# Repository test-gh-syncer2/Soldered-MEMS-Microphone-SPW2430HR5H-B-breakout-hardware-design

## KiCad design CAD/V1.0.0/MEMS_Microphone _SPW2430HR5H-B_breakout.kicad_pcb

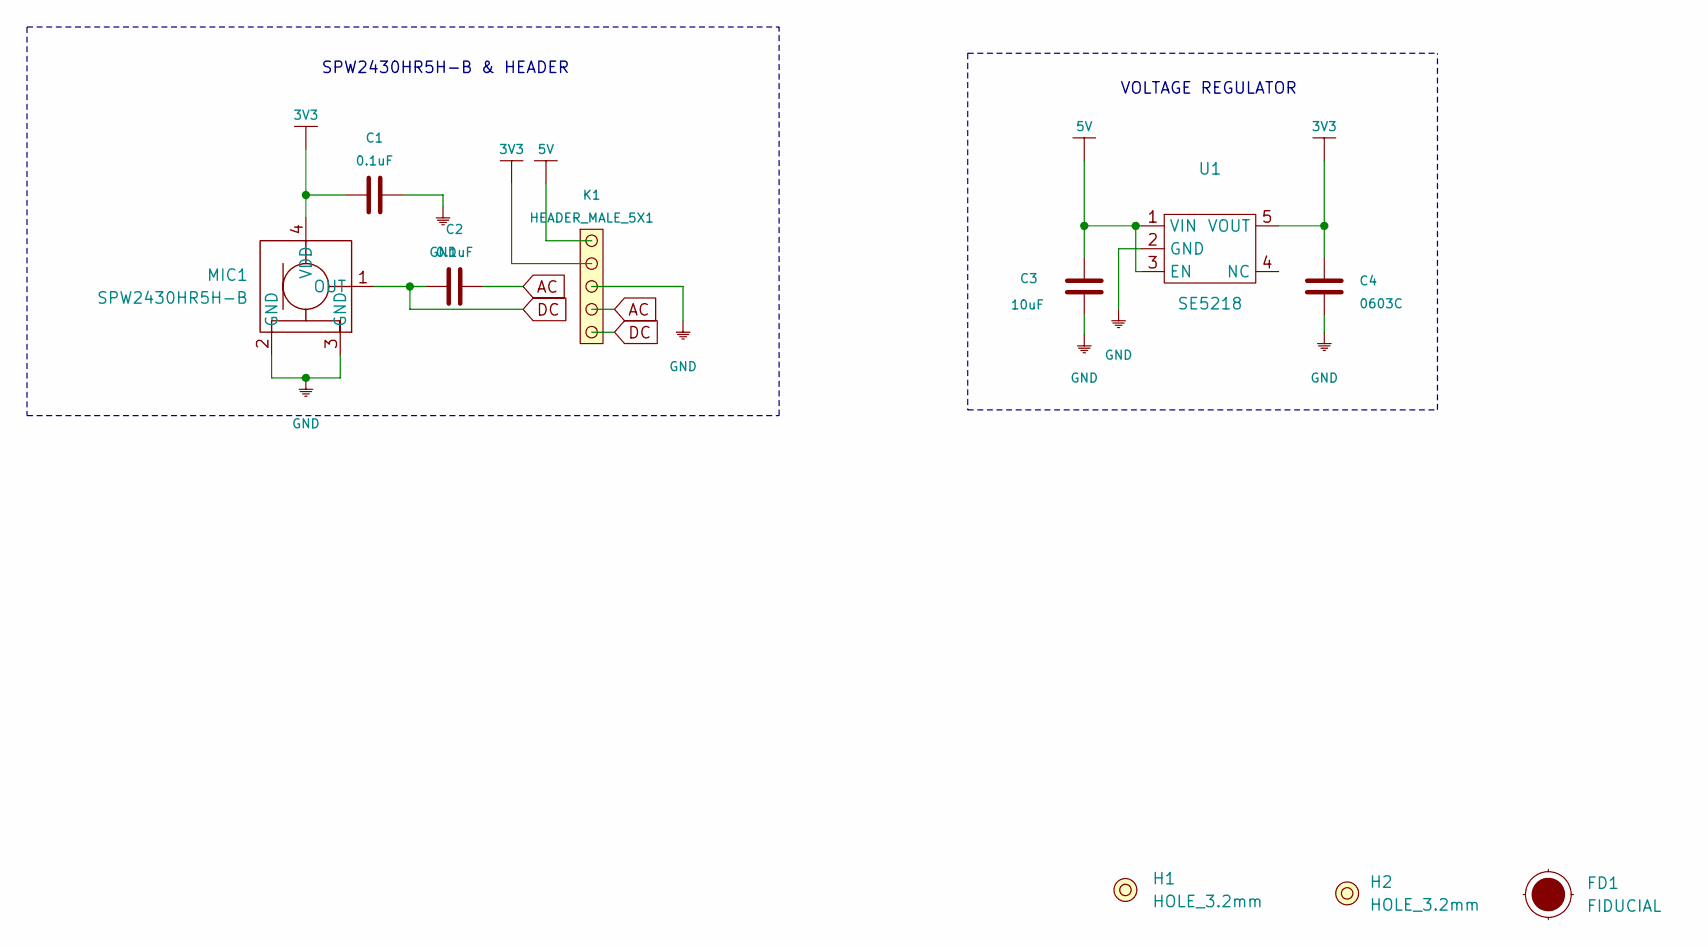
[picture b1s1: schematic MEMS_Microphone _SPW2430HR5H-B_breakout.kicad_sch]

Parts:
C1, C2: 0.1uF; 0603C
C3: 10uF; 0603C
C4: 0603C
FD1: FIDUCIAL; FIDUCIAL_23
H1, H2: HOLE_3.2mm
K1: HEADER_MALE_5X1
MIC1: SPW2430HR5H-B
U1: SE5218; SOT-23-5

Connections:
3V3: C1.1, C4.2, K1.4, MIC1.4 (VDD), U1.5 (VOUT)
5V: C3.2, K1.5, U1.1 (VIN), U1.3 (EN)
AC: C2.2, K1.2
DC: C2.1, K1.1, MIC1.1 (OUT)
GND: C1.2, C3.1, C4.1, K1.3, MIC1.2 (GND), MIC1.3 (GND), U1.2 (GND)

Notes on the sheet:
SPW2430HR5H-B & HEADER
VOLTAGE REGULATOR

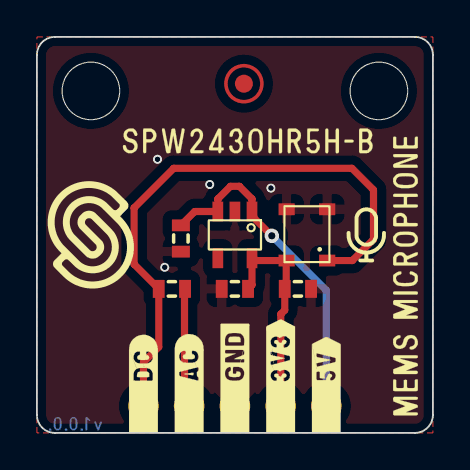
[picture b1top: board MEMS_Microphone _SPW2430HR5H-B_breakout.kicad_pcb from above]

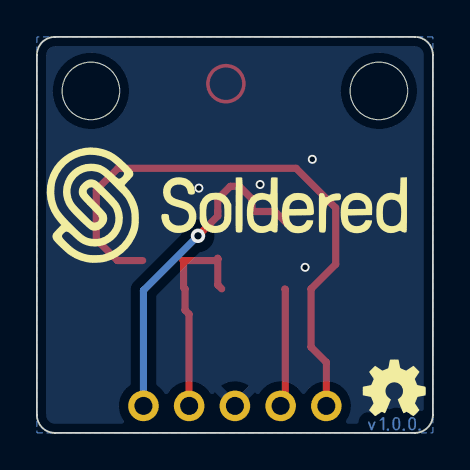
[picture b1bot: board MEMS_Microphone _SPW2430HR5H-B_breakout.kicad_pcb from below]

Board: 2 copper layers, 22.0 x 22.0 mm, 11 parts (2 on the bottom side), 5 nets.

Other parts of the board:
Ref**: Val**; Version1.0.0.

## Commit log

2021-09-23 Syncing to git
2021-09-23 Updating open source files.
